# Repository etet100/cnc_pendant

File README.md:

CNC pendant project to control my Genmitsu 4040 milling machine.

Main CHIP: ESP8266EX
AS5600 encoder based knob
3.2 inch capacitive touch display (https://www.buydisplay.com/3-2-inch-capacitive-touchscreen-240x320-tft-lcd-module-display)
I2C EEPROM for settings storage

Windows simulator/debugger

TCP Testing software:
Hercules
TcpTerminal

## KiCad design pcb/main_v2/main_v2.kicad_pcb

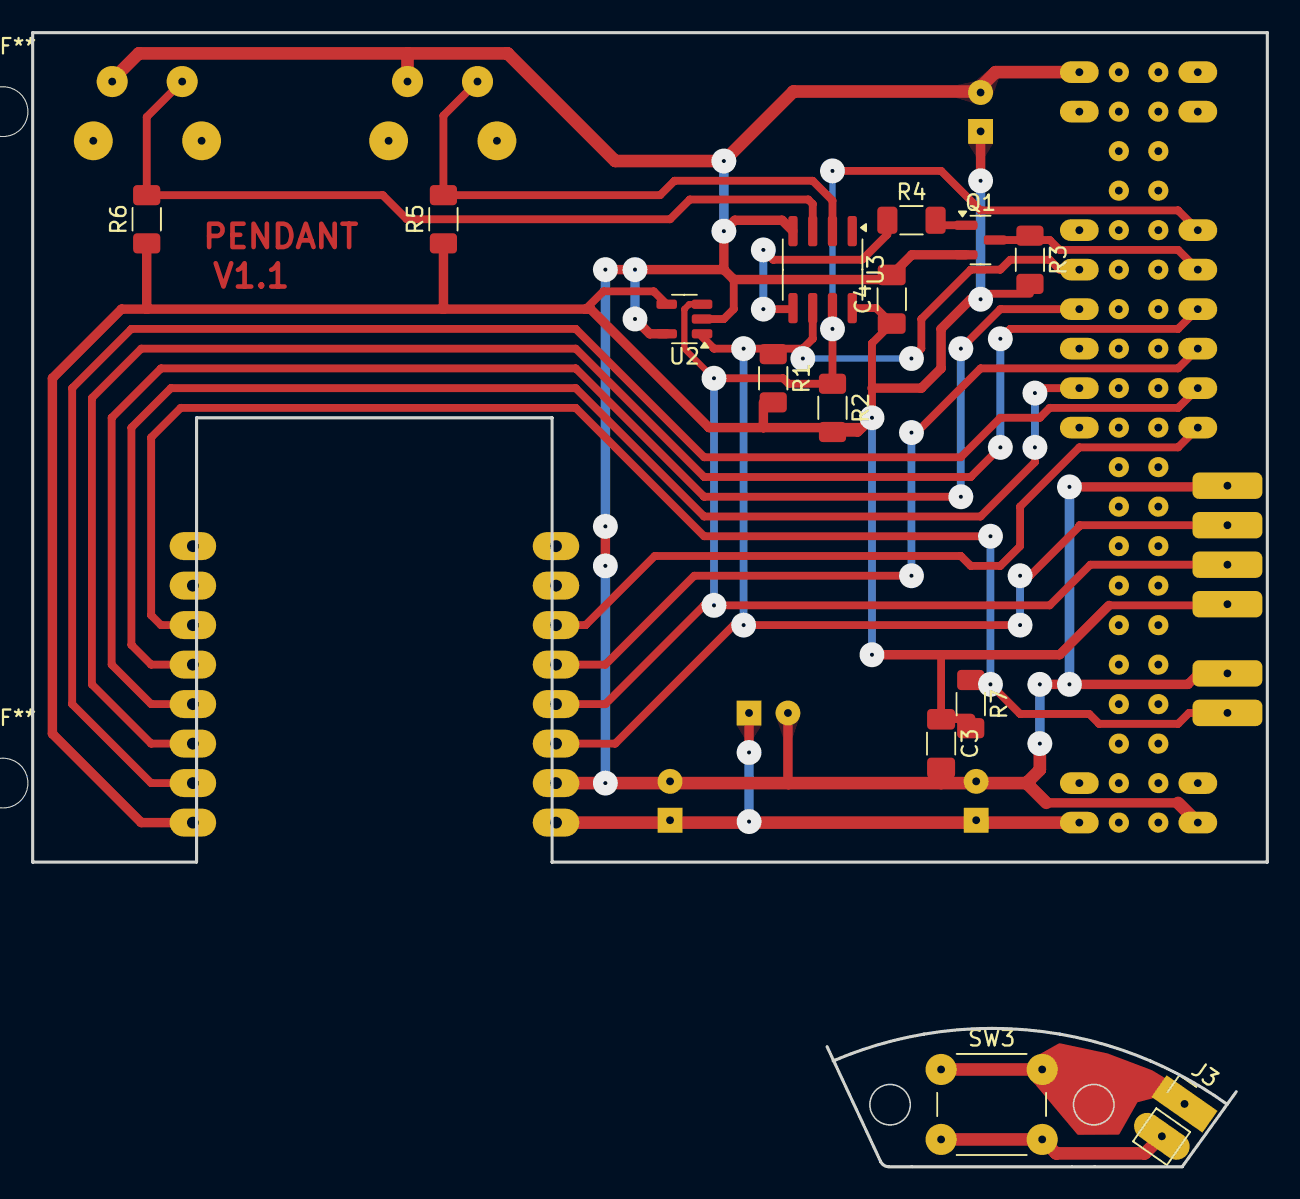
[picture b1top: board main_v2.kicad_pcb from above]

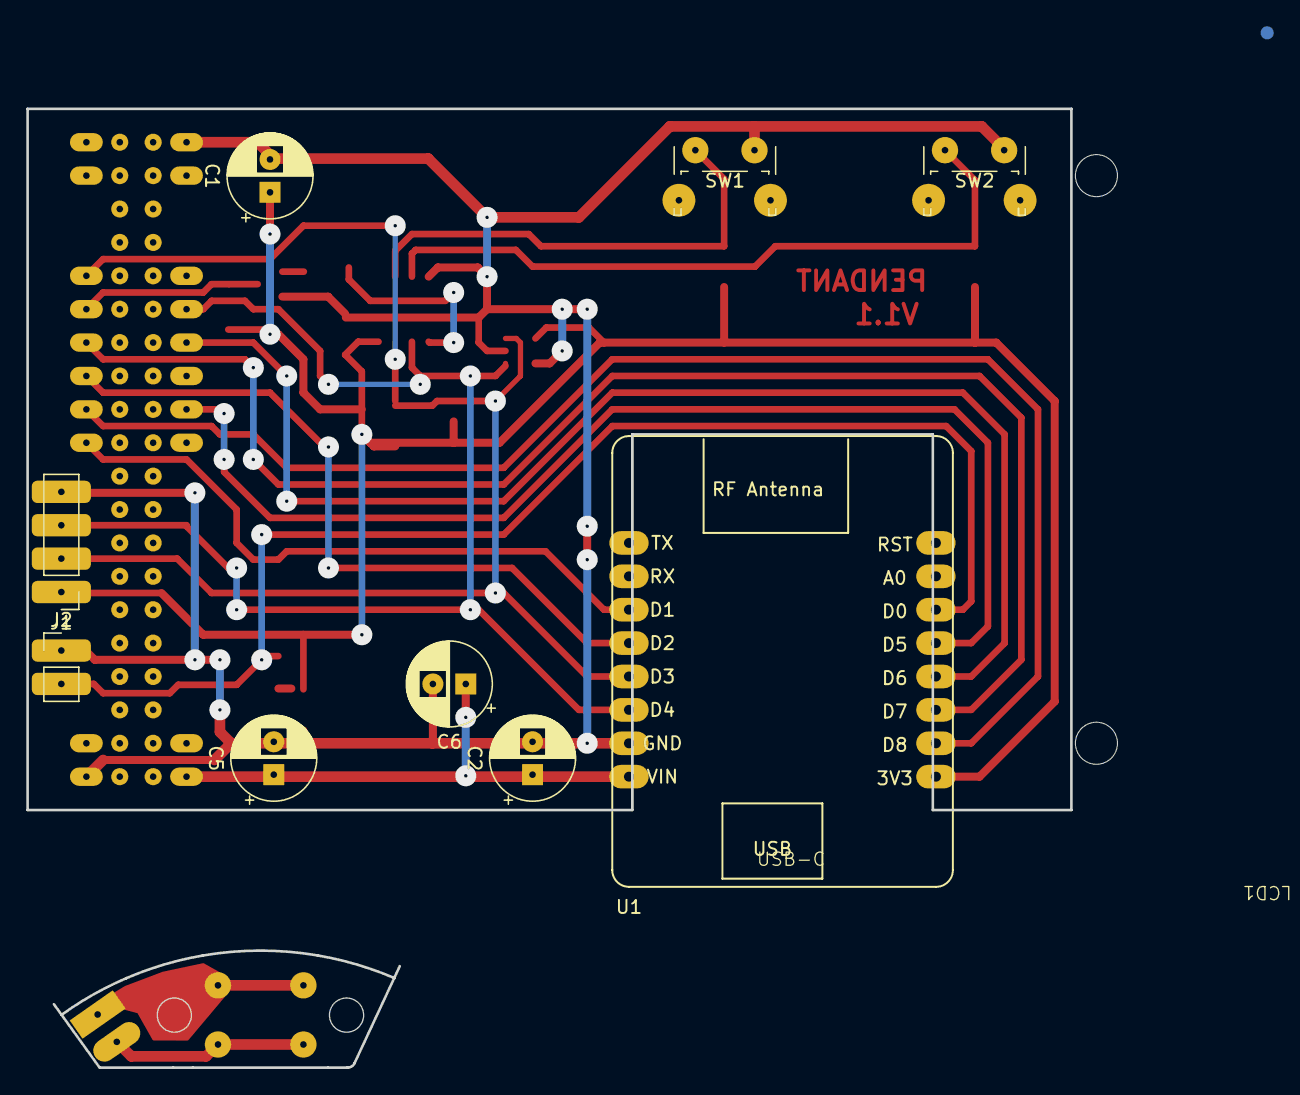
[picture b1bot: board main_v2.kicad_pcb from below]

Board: 2 copper layers, 79.4 x 53.3 mm, 24 parts (10 on the bottom side), 19 nets.

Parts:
C1, C2, C5, C6: 100uF; CP_Radial_D6.3mm_P2.50mm
C3, C4: 100n; C_1206_3216Metric_Pad1.33x1.80mm_HandSolder
J1: AS5600; PinHeader_1x04_P2.54mm_Vertical
J2, J3: Btn; PinHeader_1x02_P2.54mm_Vertical
LCD1: LCD
Q1: DMN3051L; SOT-23
R1, R2: 10k; R_1206_3216Metric_Pad1.30x1.75mm_HandSolder
R3, R5, R6, R7: 1k; R_1206_3216Metric_Pad1.30x1.75mm_HandSolder
R4: 180; R_1206_3216Metric_Pad1.30x1.75mm_HandSolder
SW1, SW2: SW_Push; SW_Tactile_SPST_Angled_PTS645Vx39-2LFS
SW3: SW_Push; SW_PUSH_6mm_H7.3mm
U1: NodeMCU_D1_Mini
U2: 24AA02-OT; SOT-23-5
U3: PCA9536D; SOIC-8_3.9x4.9mm_P1.27mm

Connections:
/SCL: J1.3, LCD1.30 (TOUCH_CLK), R1.1, U1.11 (SCL/D4), U2.1 (SCL), U3.6 (SCL)
/SDA: J1.2, LCD1.31 (TOUCH_DATA), R2.1, U1.12 (SDA/D3), U2.3 (SDA), U3.7 (SDA)
/VCC_3_3: C1.1, C3.1, C4.1, J1.1, R1.2, R2.2, R3.2, R5.1, R6.1, R7.2, U1.26 (3.3V), U2.4 (V_{CC}), U3.8 (VDD)
/VIN: C2.1, C5.1, C6.1, LCD1.2 (VCC), U1.30 (Vin)
GNDD: C1.2, C2.2, C3.2, C4.2, C5.2, C6.2, J1.4, J2.1, LCD1.1 (GND), LCD1.40 (GND), Q1.2 (S), SW1.2, SW2.2, U1.2 (GND), U2.2 (V_{SS}), U2.5 (WP), U3.4 (VSS)
unnamed: J2.2, R7.1, U1.15 (D0)
unnamed: J3.1, SW3.1
unnamed: J3.2, SW3.2
unnamed: LCD1.29 (LCD_BACKL), Q1.3 (D), R3.1
unnamed: LCD1.24 (LCD_CLK), U1.8 (D5)
unnamed: LCD1.23 (LCD_CS), U1.5 (D8)
unnamed: LCD1.25 (LCD_DC), U1.13 (D2)
unnamed: LCD1.27 (LCD_SDI), U1.6 (D7)
unnamed: LCD1.28 (LCD_SDO), U1.7 (D6)
unnamed: LCD1.21 (RST), U1.14 (D1)
unnamed: Q1.1 (G), R4.2
unnamed: R5.2, SW1.1, U3.2 (IO1)
unnamed: R6.2, SW2.1, U3.3 (IO2)
unnamed: R4.1, U3.5 (IO3)

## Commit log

2024-05-03 Scan WiFi, read AS5600
2024-05-03 GUIslice, something on screen
2024-05-03 160Mhz, enabled wifi and as5600
2024-05-26 Testing adafruit gfx, nbSPI
2024-05-27 Convert images
2024-05-27 clang-format
2024-05-27 main.cpp and images
2024-05-27 Documents
2024-05-27 Remove guislice
2024-05-27 Font converter, testing fonts
2024-05-27 Drawing number, set rotation and fill screen
2024-05-30 Testing WiFi, images, smaller font
2024-05-30 Testing touch
2024-05-30 Removed GFX tests
2024-05-31 Touch almost working
2024-06-01 Classes / modules
2024-06-02 More cleanup
2024-06-02 Removed old code
2024-06-02 Wheel class
2024-06-02 Readme
2024-06-02 Debug logs, initial version of main screen
2024-06-02 Find toched zone, padd numbers with zeros, draw numbers
2024-06-29 pcb - lcd on wrong side
2024-07-23 Buttons, drawing float, State, touch pos
2024-08-02 logo
2024-08-02 wheel position with hysteresis
2024-08-02 logs
2024-08-02 spi freq
2024-08-02 i2c eeprom test
2024-08-02 screen init moved
2024-08-02 eeprom dependency
2024-08-02 50ms update
2024-08-11 Async TCP
2024-08-11 Drawing XYZ
2024-08-11 Fixed initital wheel position
2024-08-11 PCB - small board
2024-08-23 Testing communication, buffers, wifi
2024-08-30 Fonts, buttons
2024-08-30 Testing communication, crc, circular buffer
2024-08-30 Font manolomono
2024-08-30 Wheel - do more than one step at a ti me
2024-09-02 Images - new format
2024-09-02 Almost finished main screen, major changes
2024-09-06 Animation, selected axis, centering text, touchzones
2024-09-07 html projects, generate colors, fill rect, setTextColor
2024-09-14 Events manager, optimized drawing, fontawesome, optimizations everywhere
2025-02-25 Qt Simulator
2025-02-25 Fonts
2025-03-08 Popup window, refactor drawing
